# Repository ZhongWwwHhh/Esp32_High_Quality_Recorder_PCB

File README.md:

# Esp32_High_Quality_Recorder_PCB
PCB design for Esp32_High_Quality_Recorder

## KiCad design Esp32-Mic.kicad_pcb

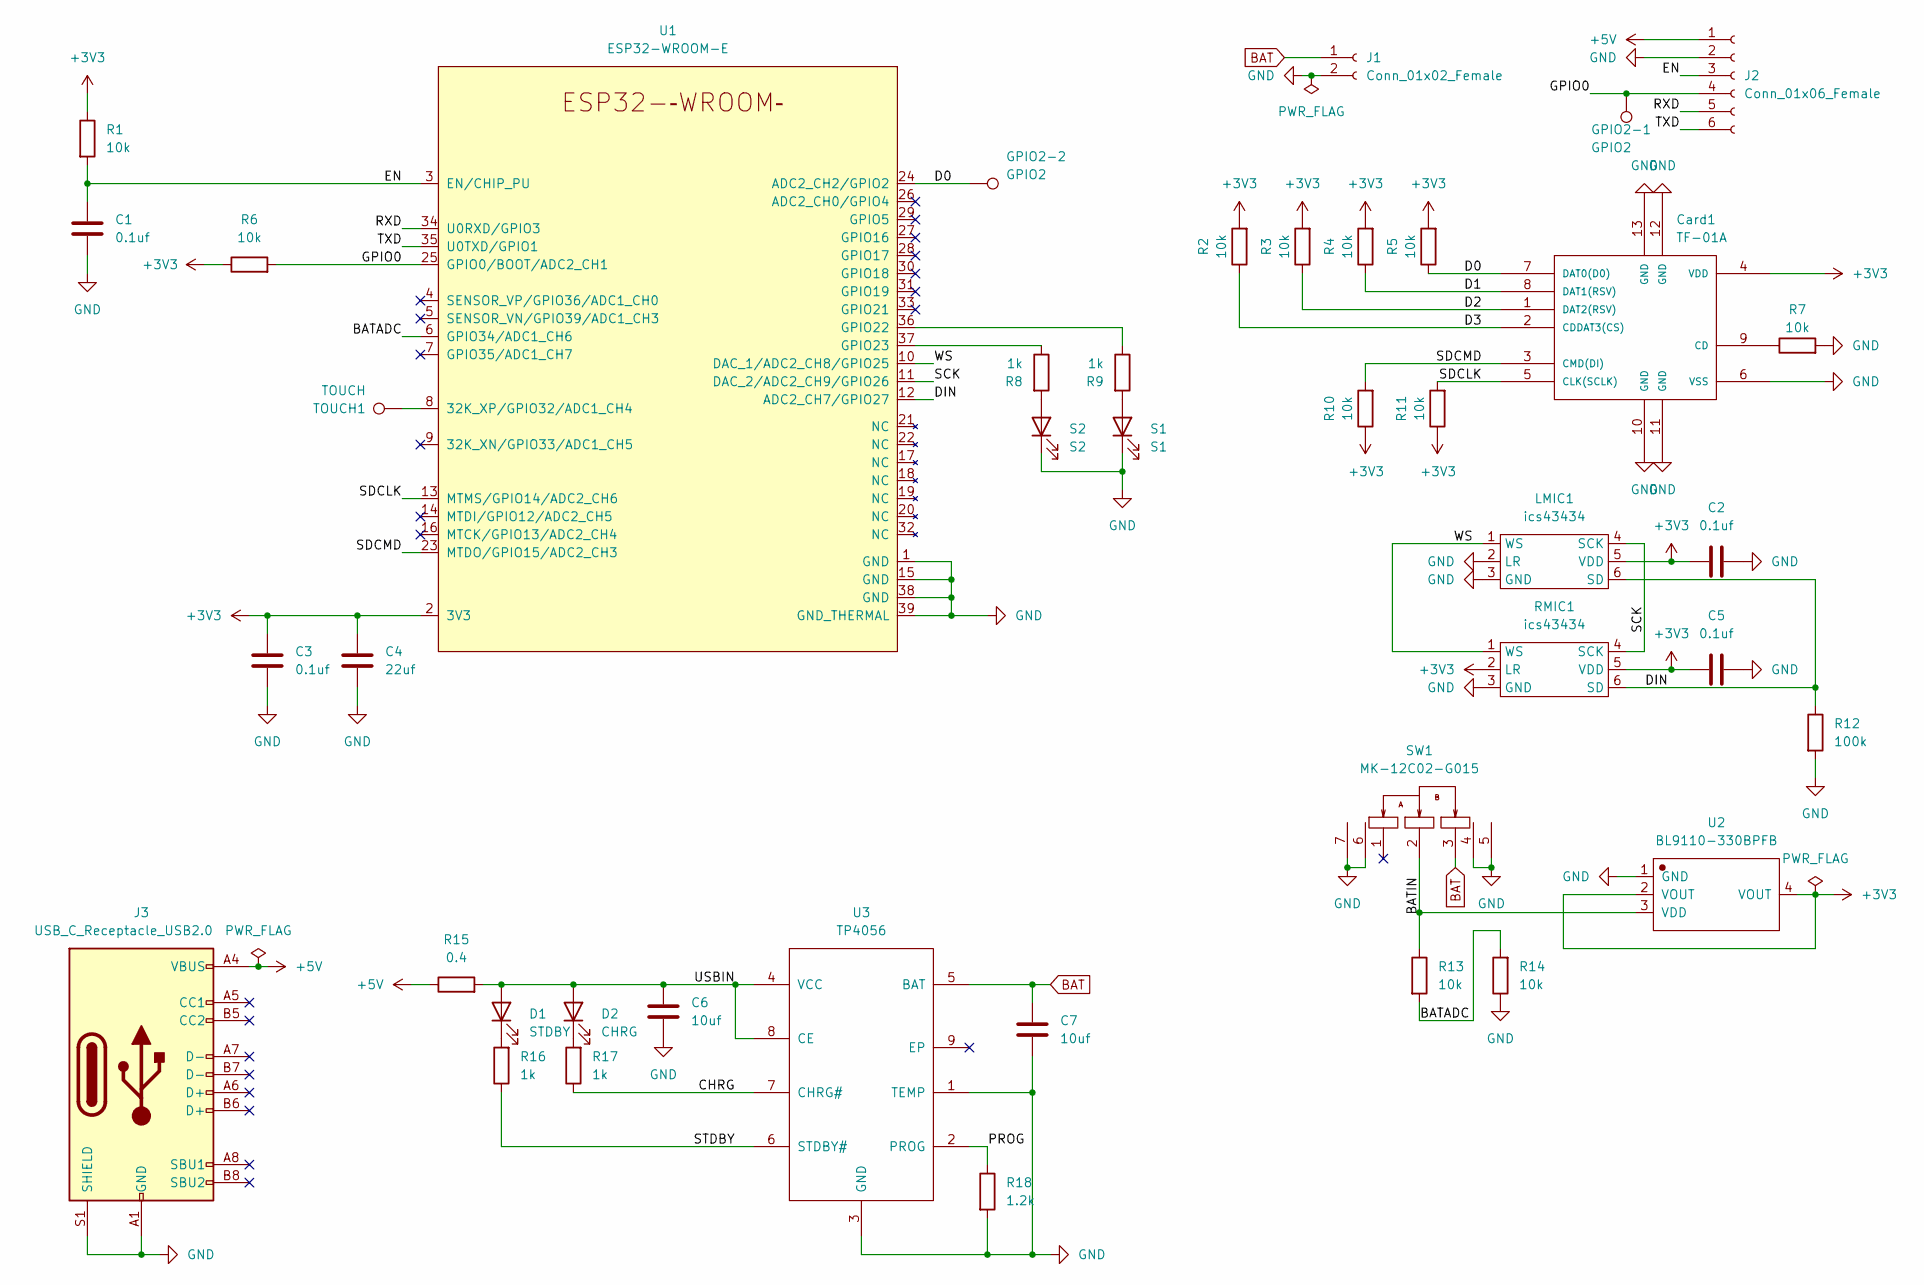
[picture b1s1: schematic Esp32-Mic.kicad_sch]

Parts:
C1, C2, C3, C5: 0.1uf; C_0402_1005Metric; MPN C1525
C4: 22uf; C_0603_1608Metric; MPN C59461
C6, C7: 10uf; C_0603_1608Metric; MPN C19702
Card1: TF-01A; TF-SMD_TF-01A; MPN C91145
D1: STDBY; LED_0603_1608Metric; MPN C72041
D2: CHRG; LED_0603_1608Metric; MPN C72041
GPIO2-1, GPIO2-2: GPIO2; TestPoint_Pad_D1.0mm
J1: Conn_01x02_Female; PinHeader_1x02_P2.54mm_Vertical
J2: Conn_01x06_Female; PinHeader_1x06_P2.00mm_Vertical
J3: USB_C_Receptacle_USB2.0; USB_C_Receptacle_HRO_TYPE-C-31-M-12; MPN C2927038
LMIC1: ics43434
R1, R2, R3, R4, R5, R6, R7, R10, R11, R13, R14: 10k; R_0603_1608Metric; MPN C25804
R8, R9, R16, R17: 1k; R_0603_1608Metric; MPN C21190
R12: 100k; R_0603_1608Metric; MPN C25803
R15: 0.4; R_2512_6332Metric; MPN C421561
R18: 1.2k; R_0603_1608Metric; MPN C22765
RMIC1: ics43434
S1: S1; LED_0603_1608Metric; MPN C72041
S2: S2; LED_0603_1608Metric; MPN C72041
SW1: MK-12C02-G015; SW-SMD_G-SWITCH_MK-12C02-G015; MPN C2911519
TOUCH1: TOUCH; TestPoint_Pad_4.0x4.0mm
U1: ESP32-WROOM-E; ESP32-WROOM-32E; MPN C701341
U2: BL9110-330BPFB; SOT-223_L6.5-W3.5-P2.30-LS7.0-BR; MPN C169246
U3: TP4056; ESOP-8_L4.9-W3.9-P1.27-LS6.0-BL-EP; MPN C16581

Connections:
+3V3: C2.1, C3.1, C4.1, C5.1, Card1.4 (VDD), LMIC1.5 (VDD), R1.1, R2.2, R3.2, R4.2, R5.2, R6.1, R10.1, R11.1, RMIC1.2 (LR), RMIC1.5 (VDD), U1.2 (3V3), U2.2 (VOUT), U2.4 (VOUT)
+5V: J2.1, J3.A4 (VBUS), J3.A9 (VBUS), J3.B4 (VBUS), J3.B9 (VBUS), R15.1
/BATADC: R13.2, R14.2, U1.6 (GPIO34/ADC1_CH6)
/BATIN: R13.1, SW1.2, U2.3 (VDD)
/CHRG: R17.1, U3.7 (CHRG#)
/D0: Card1.7 (DAT0(D0)), GPIO2-2.1, R5.1, U1.24 (ADC2_CH2/GPIO2)
/D1: Card1.8 (DAT1(RSV)), R4.1
/D2: Card1.1 (DAT2(RSV)), R3.1
/D3: Card1.2 (CDDAT3(CS)), R2.1
/DIN: LMIC1.6 (SD), R12.1, RMIC1.6 (SD), U1.12 (ADC2_CH7/GPIO27)
/EN: C1.1, J2.3, R1.2, U1.3 (EN/CHIP_PU)
/GPIO0: GPIO2-1.1, J2.4, R6.2, U1.25 (GPIO0/BOOT/ADC2_CH1)
/PROG: R18.1, U3.2 (PROG)
/RXD: J2.5, U1.34 (U0RXD/GPIO3)
/SCK: LMIC1.4 (SCK), RMIC1.4 (SCK), U1.11 (DAC_2/ADC2_CH9/GPIO26)
/SDCLK: Card1.5 (CLK(SCLK)), R11.2, U1.13 (MTMS/GPIO14/ADC2_CH6)
/SDCMD: Card1.3 (CMD(DI)), R10.2, U1.23 (MTDO/GPIO15/ADC2_CH3)
/STDBY: R16.1, U3.6 (STDBY#)
/TXD: J2.6, U1.35 (U0TXD/GPIO1)
/USBIN: C6.2, D1.2 (A), D2.2 (A), R15.2, U3.4 (VCC), U3.8 (CE)
/WS: LMIC1.1 (WS), RMIC1.1 (WS), U1.10 (DAC_1/ADC2_CH8/GPIO25)
BAT: C7.1, J1.1, SW1.3, U3.5 (BAT)
GND: C1.2, C2.2, C3.2, C4.2, C5.2, C6.1, C7.2, Card1.6 (VSS), Card1.10 (GND), Card1.11 (GND), Card1.12 (GND), Card1.13 (GND), J1.2, J2.2, J3.A1 (GND), J3.A12 (GND), J3.B1 (GND), J3.B12 (GND), J3.S1 (SHIELD), LMIC1.2 (LR), LMIC1.3 (GND), R7.2, R12.2, R14.1, R18.2, RMIC1.3 (GND), S1.1 (K), S2.1 (K), SW1.4, SW1.5, SW1.6, SW1.7, U1.1 (GND), U1.15 (GND), U1.38 (GND), U1.39 (GND_THERMAL), U2.1 (GND), U3.1 (TEMP), U3.3 (GND)
unnamed: Card1.9 (CD), R7.1
unnamed: D1.1 (K), R16.2
unnamed: D2.1 (K), R17.2
unnamed: R8.1, U1.37 (GPIO23)
unnamed: R8.2, S2.2 (A)
unnamed: R9.1, U1.36 (GPIO22)
unnamed: R9.2, S1.2 (A)
unnamed: TOUCH1.1, U1.8 (32K_XP/GPIO32/ADC1_CH4)

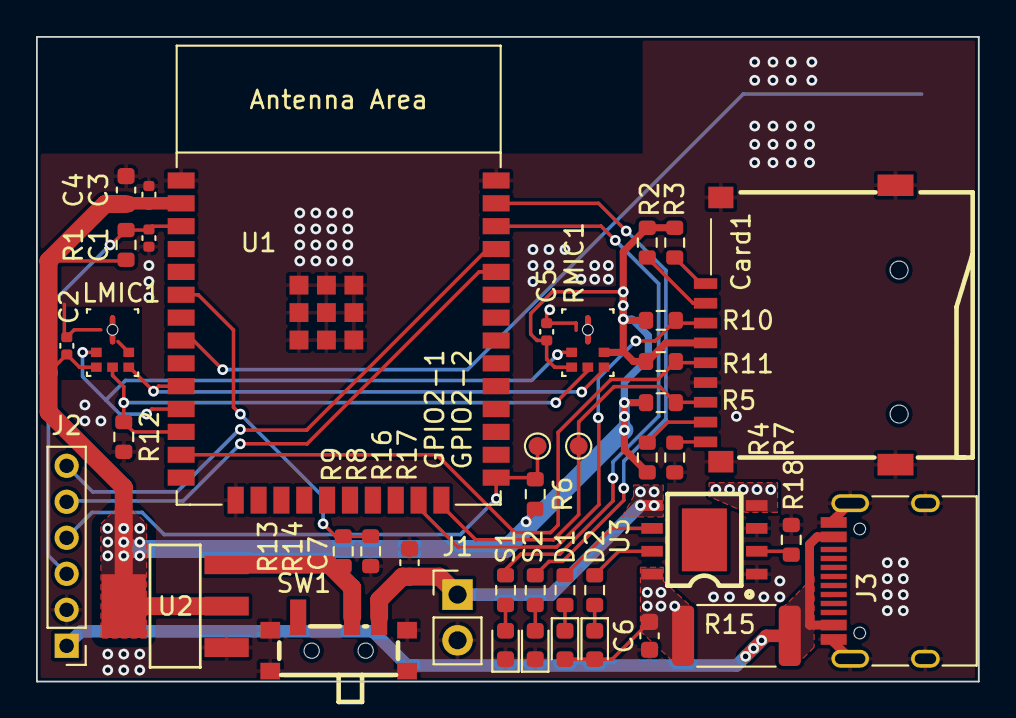
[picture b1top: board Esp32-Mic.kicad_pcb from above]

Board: 2 copper layers, 52.3 x 35.8 mm, 42 parts (1 on the bottom side), 31 nets.

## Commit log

2022-10-01 1.0 original init
